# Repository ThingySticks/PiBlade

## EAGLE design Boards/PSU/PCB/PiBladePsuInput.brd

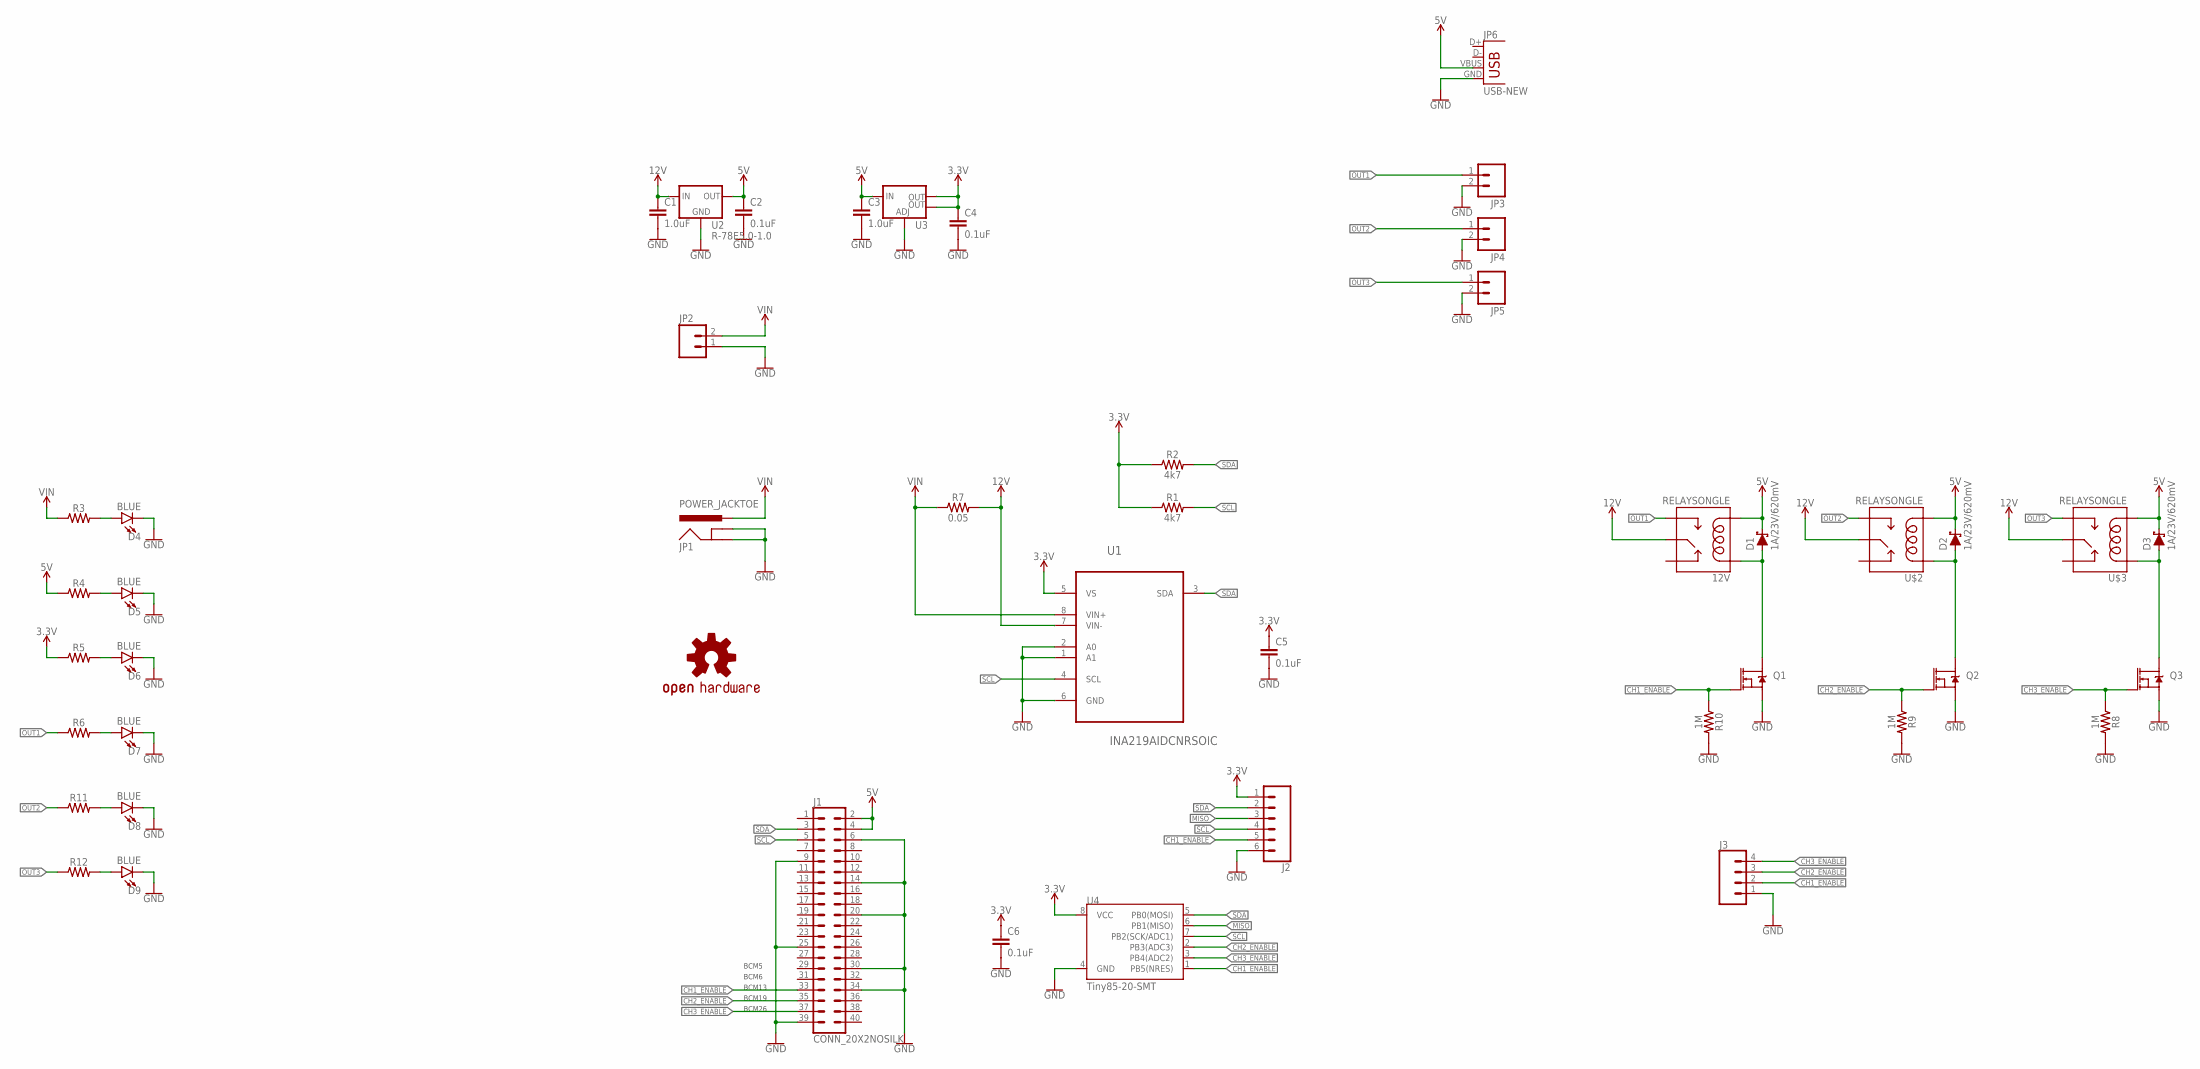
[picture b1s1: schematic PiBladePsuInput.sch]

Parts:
12V: RELAYSONGLE; SRD-5VDC-SL-C
C1, C3: 1.0uF; 0805
C2, C4, C5, C6: 0.1uF; 0805
D1, D2, D3: 1A/23V/620mV; SOD-323
D4, D5, D6, D7, D8, D9: BLUE; LED-1206
J1: CONN_20X2NOSILK; 2X20_NOSILK
J2: CONN_06SMD-1MM; 1X06-1MM
J3: CONN_04SMD2; 1X04_1MM_RA
JP1: POWER_JACKTOE; POWER_JACK_SMD_OVERPASTE_TOE
JP2, JP3, JP4, JP5: M025MM; SCREWTERMINAL-5MM-2
JP6: USB-NEW; USB-A-VERTICAL
LOGO1: OSHW-LOGOM; OSHW-LOGO-M
Q1, Q2, Q3: 220mA/50V/3.5Ω; SOT23-3
R1, R2: 4k7; 0805
R3, R4, R5, R6, R11, R12: 0805
R7: 0.05; 2512
R8, R9, R10: 1M; 0805
U1: INA219AIDCNRSOIC; SO08
U2: R-78E5.0-1.0; DC-DC_CONVERTER_78XX
U3: V_REG_LM1117SOT223; SOT223
U4: Tiny85-20-SMT; SO08-EIAJ
U$2, U$3: RELAYSONGLE; SRD-5VDC-SL-C

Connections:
3.3V: C4.1, C5.1, C6.1, J2.1, R1.1, R2.1, R5.1, U1.5 (VS), U3.2 (OUT), U3.4 (OUT), U4.8 (VCC)
5V: 12V.COIL2, C2.1, C3.1, D1.C, D2.C, D3.C, J1.2, J1.4, JP6.VBUS, R4.1, U2.VOUT (OUT), U3.3 (IN), U$2.COIL2, U$3.COIL2
12V: 12V.COMMON (MAIN), C1.1, R7.P$2 (2), U1.7 (VIN-), U2.VIN (IN), U$2.COMMON (MAIN), U$3.COMMON (MAIN)
CH1_ENABLE: J1.33, J2.5, J3.2, Q1.1 (G), R10.1, U4.1 (PB5(NRES))
CH2_ENABLE: J1.35, J3.3, Q2.1 (G), R9.1, U4.2 (PB3(ADC3))
CH3_ENABLE: J1.37, J3.4, Q3.1 (G), R8.1, U4.3 (PB4(ADC2))
GND: C1.2, C2.2, C3.2, C4.2, C5.2, C6.2, D4.C, D5.C, D6.C, D7.C, D8.C, D9.C, J1.6, J1.9, J1.14, J1.20, J1.25, J1.30, J1.34, J1.39, J2.6, J3.1, JP1.GND (GNDBREAK), JP1.P$4 (GND), JP2.1, JP3.2, JP4.2, JP5.2, JP6.GND, Q1.2 (S), Q2.2 (S), Q3.2 (S), R8.2, R9.2, R10.2, U1.1 (A1), U1.2 (A0), U1.6 (GND), U2.GND, U3.1 (ADJ), U4.4 (GND)
MISO: J2.3, U4.6 (PB1(MISO))
unnamed: D4.A, R3.2
unnamed: D6.A, R5.2
unnamed: D7.A, R6.2
unnamed: D5.A, R4.2
unnamed: D8.A, R11.2
unnamed: D9.A, R12.2
unnamed: D3.A, Q3.3 (D), U$3.COIL1
unnamed: D2.A, Q2.3 (D), U$2.COIL1
unnamed: 12V.COIL1, D1.A, Q1.3 (D)
OUT1: 12V.OPEN (NO), JP3.1, R6.1
OUT2: JP4.1, R11.1, U$2.OPEN (NO)
OUT3: JP5.1, R12.1, U$3.OPEN (NO)
SCL: J1.5, J2.4, R1.2, U1.4 (SCL), U4.7 (PB2(SCK/ADC1))
SDA: J1.3, J2.2, R2.2, U1.3 (SDA), U4.5 (PB0(MOSI))
VIN: JP1.VIN0 (PWR), JP2.2, R3.1, R7.P$1 (1), U1.8 (VIN+)

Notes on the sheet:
BCM13
BCM6
BCM5
BCM26
BCM19

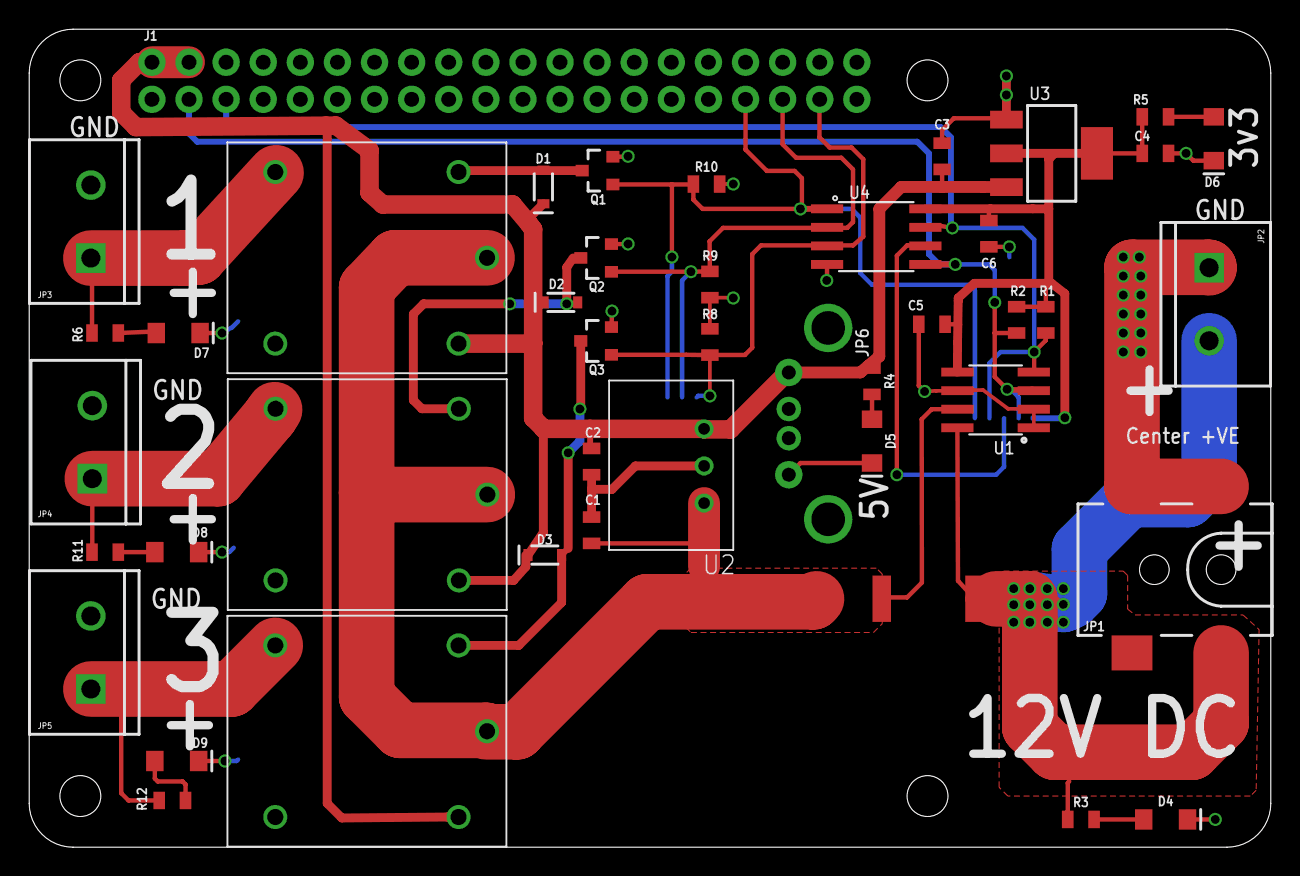
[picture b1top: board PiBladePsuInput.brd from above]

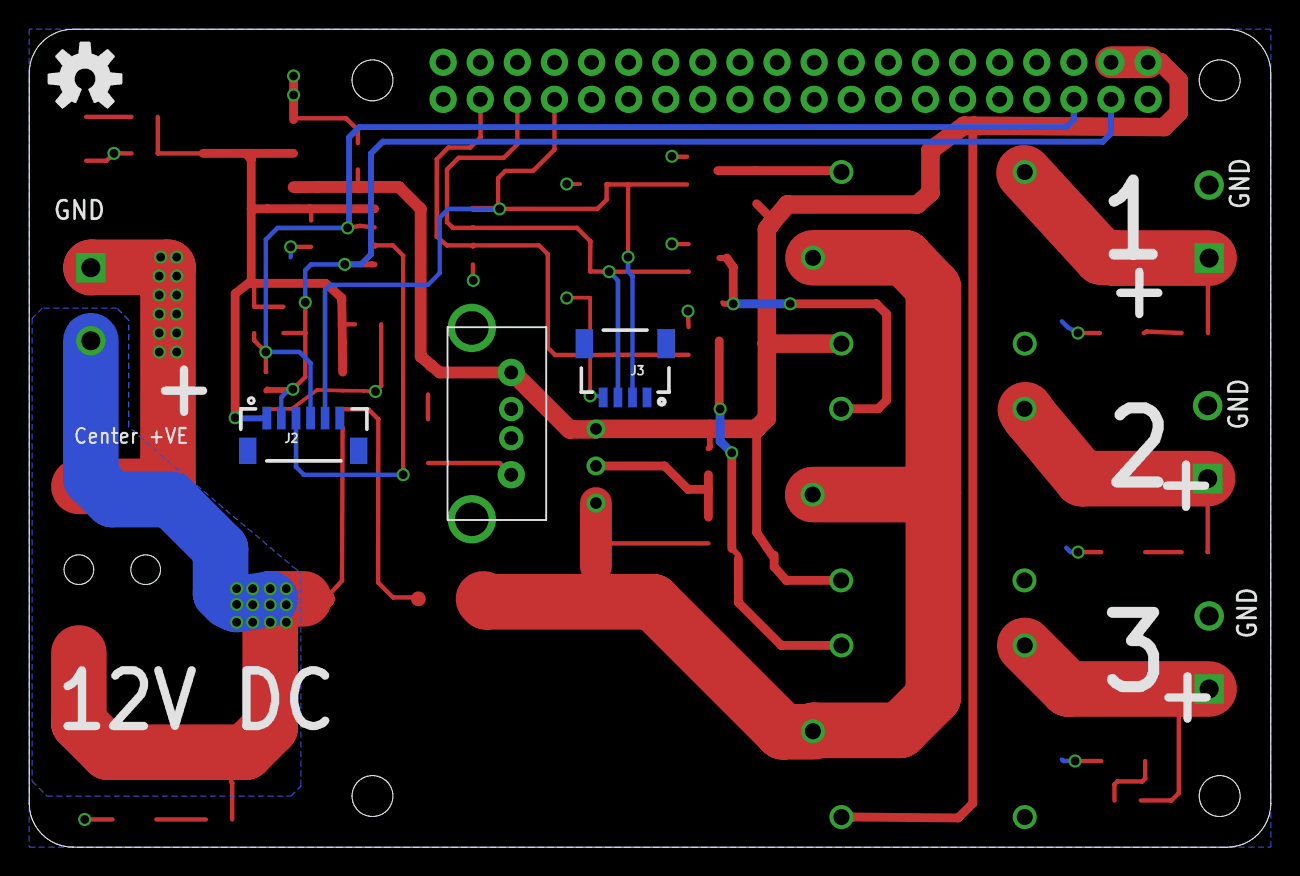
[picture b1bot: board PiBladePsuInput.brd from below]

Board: 2 copper layers, 85.0 x 56.0 mm, 47 parts (2 on the bottom side), 23 nets.

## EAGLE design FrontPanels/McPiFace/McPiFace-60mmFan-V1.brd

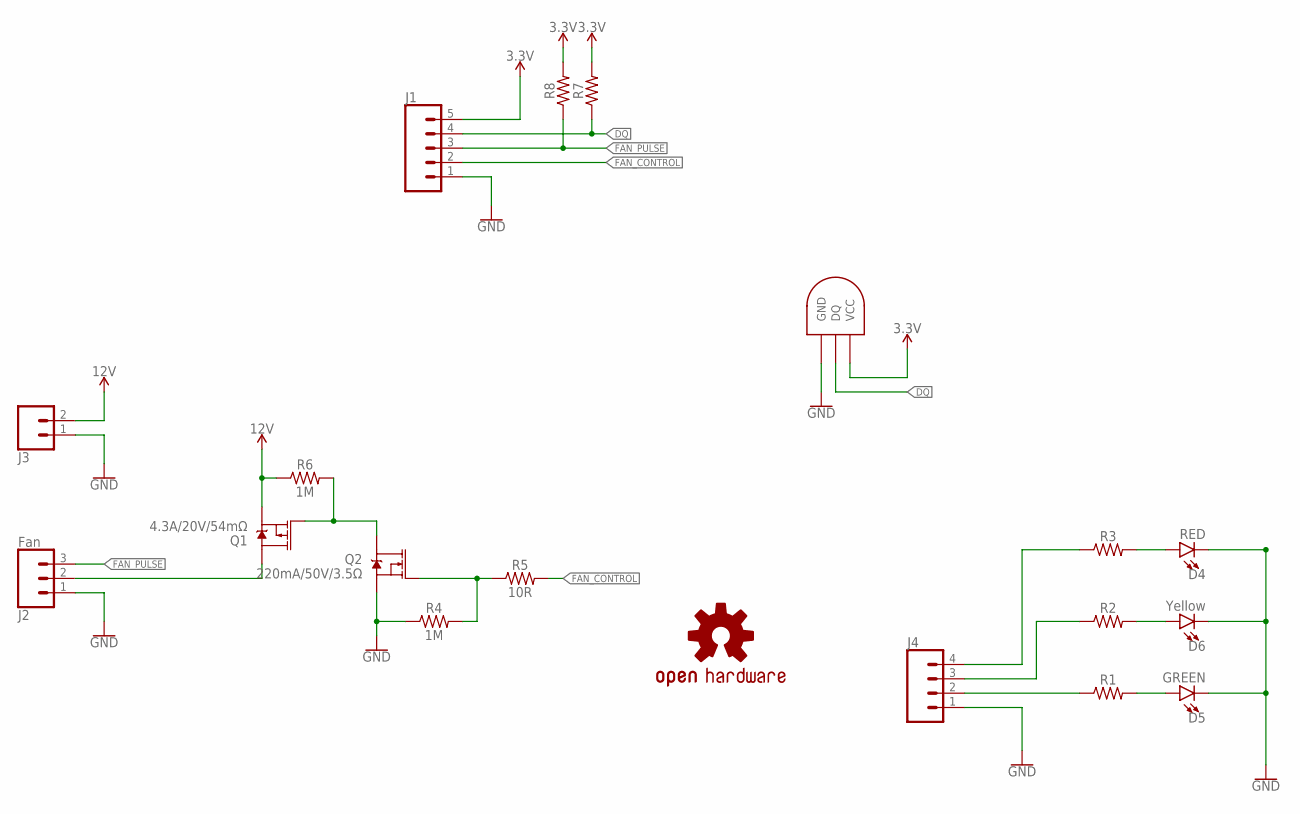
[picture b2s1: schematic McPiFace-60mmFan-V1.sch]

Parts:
D4: RED; LED-1206
D5: GREEN; LED-1206
D6: Yellow; LED-1206
J1: CONN_05SMD; 1X05_1MM
J2: Fan; JST-3-SMD
J3: CONN_02-JST-2MM-SMT; JST-2-SMD
J4: CONN_04SMD2; 1X04_1MM_RA
LOGO1: OSHW-LOGOL; OSHW-LOGO-L
Q1: 4.3A/20V/54mΩ; SOT23-3
Q2: 220mA/50V/3.5Ω; SOT23-3
R1, R2, R3: 1206
R4, R6: 1M; 0805
R5: 10R; 0805
R7, R8: 0805
U$1: DS1820SOIC; DS18B20_SOIC

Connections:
3.3V: J1.5, R7.2, R8.2, U$1.VCC
12V: J3.2 (1), Q1.2 (S), R6.1
DQ: J1.4, R7.1, U$1.DQ
FAN_CONTROL: J1.2, R5.2
FAN_PULSE: J1.3, J2.3 (1), R8.1
GND: D4.C, D5.C, D6.C, J1.1, J2.1 (3), J3.1 (2), J4.1, Q2.2 (S), R4.1, U$1.GND
unnamed: D4.A, R3.2
unnamed: D6.A, R2.2
unnamed: D5.A, R1.2
unnamed: J4.2, R1.1
unnamed: J4.3, R2.1
unnamed: J4.4, R3.1
unnamed: J2.2, Q1.3 (D)
unnamed: Q1.1 (G), Q2.3 (D), R6.2
unnamed: Q2.1 (G), R4.2, R5.1

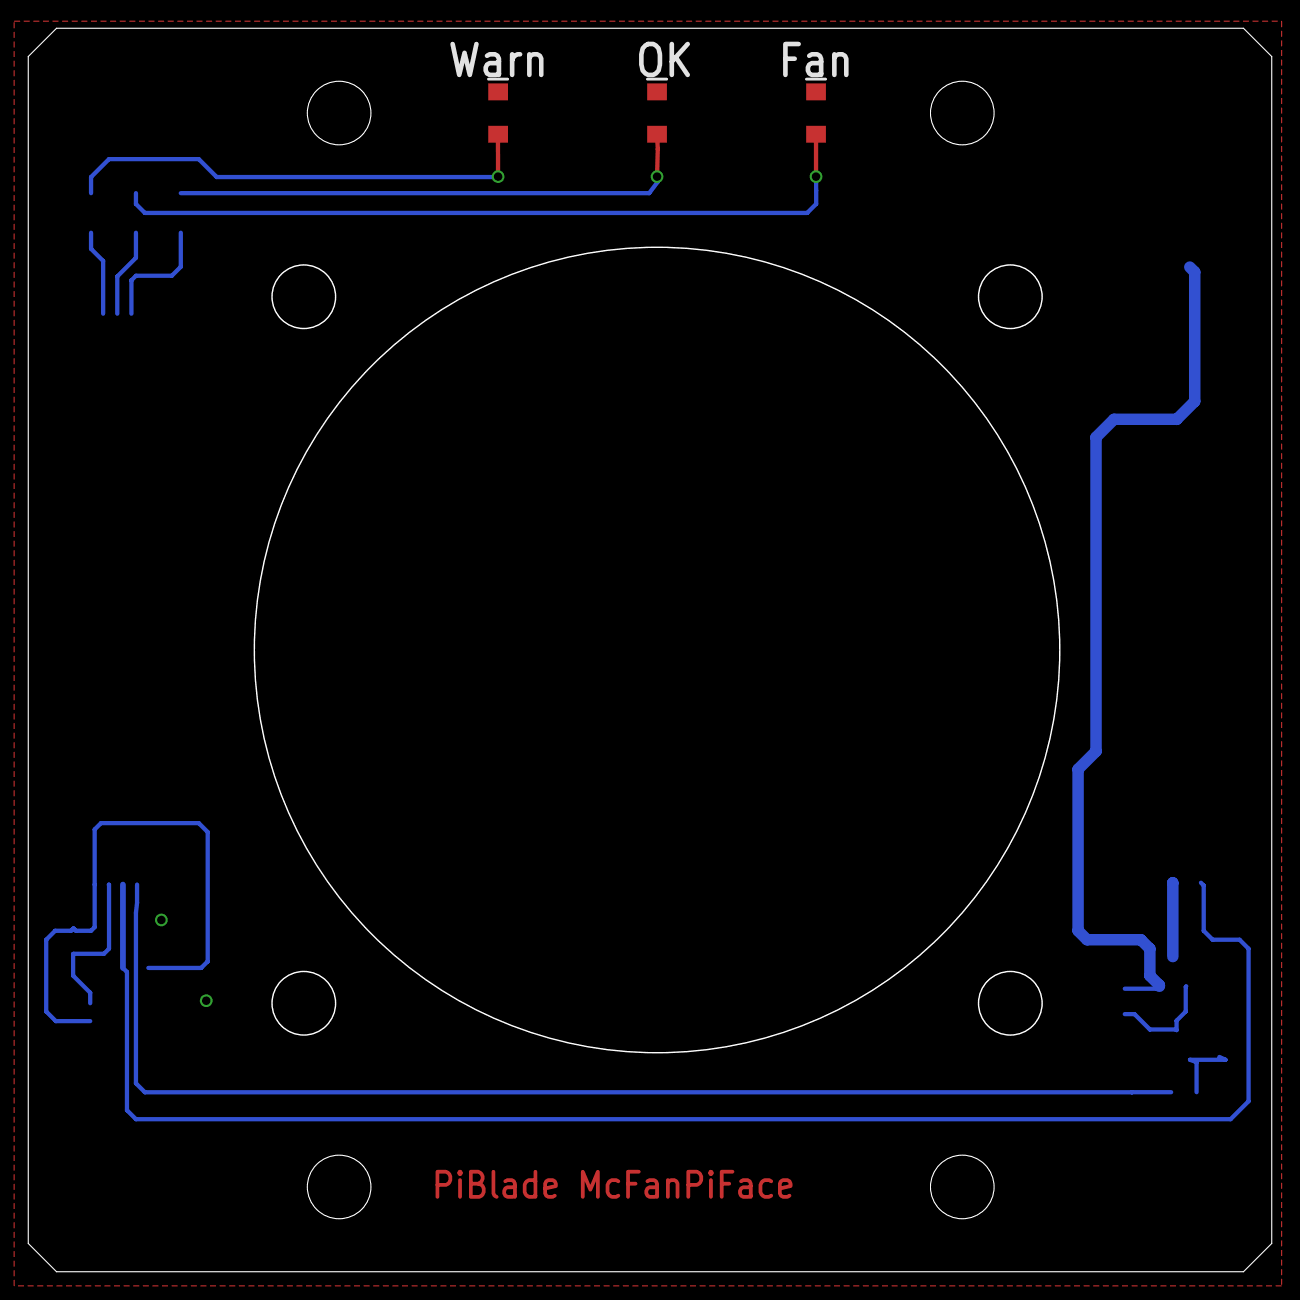
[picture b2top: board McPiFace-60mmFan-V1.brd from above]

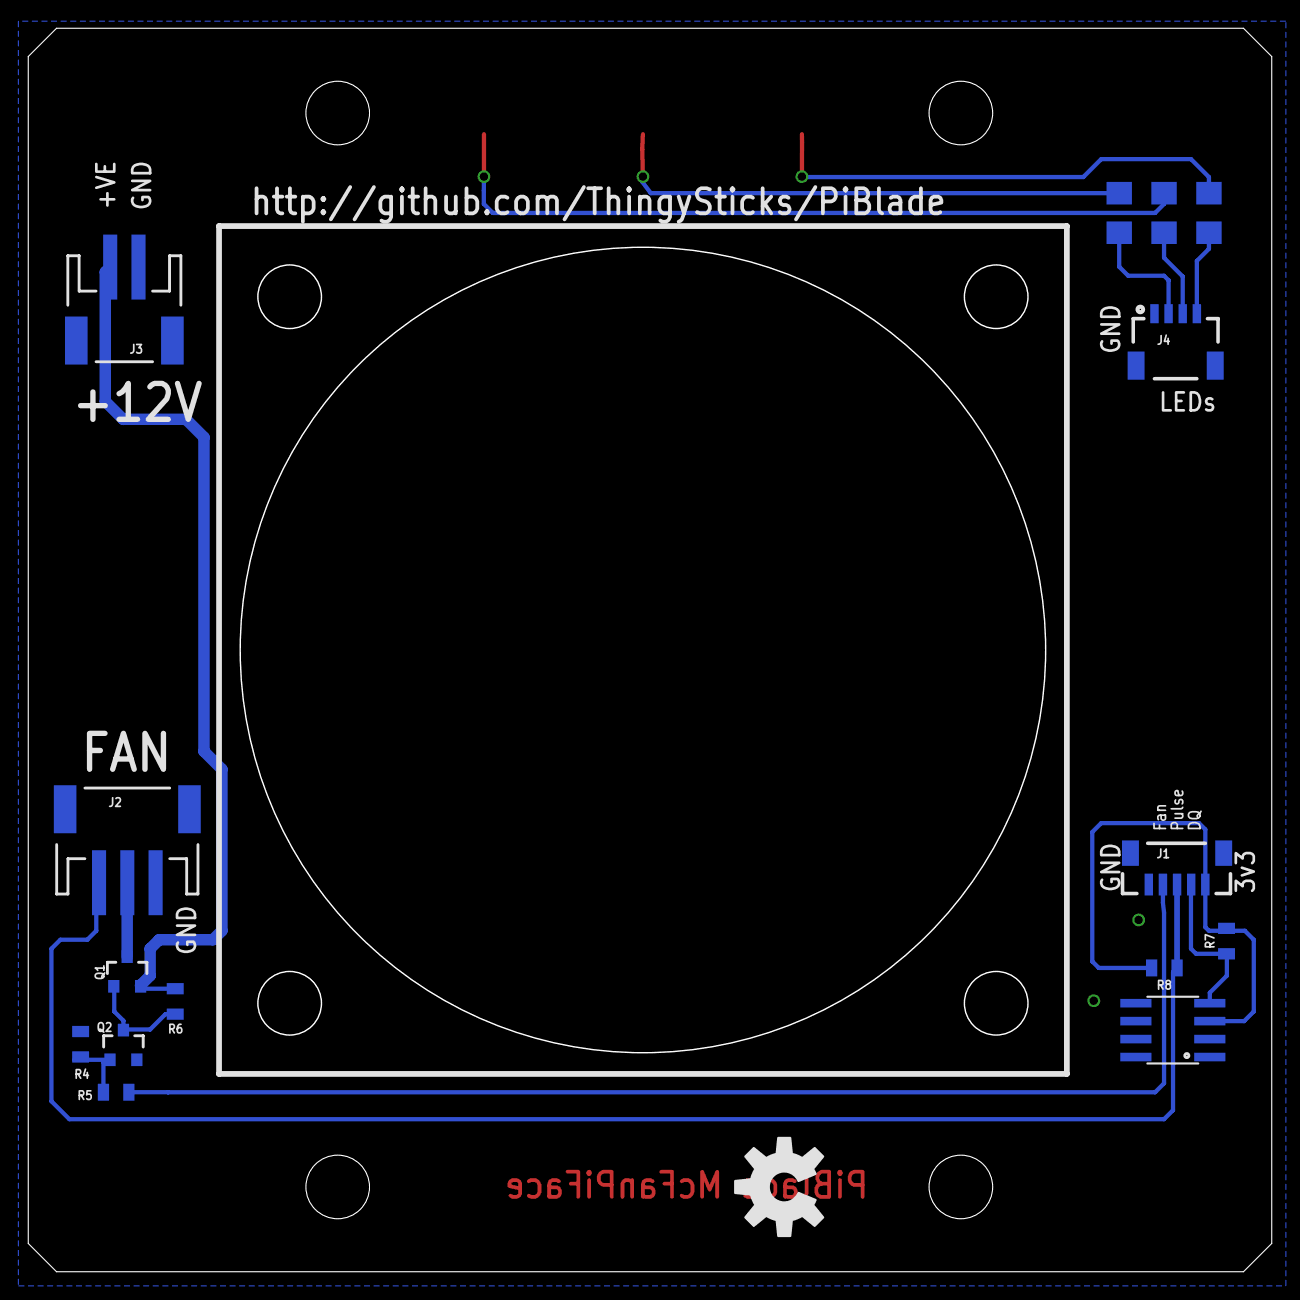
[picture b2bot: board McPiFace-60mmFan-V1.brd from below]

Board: 2 copper layers, 88.0 x 88.0 mm, 19 parts (16 on the bottom side), 15 nets.

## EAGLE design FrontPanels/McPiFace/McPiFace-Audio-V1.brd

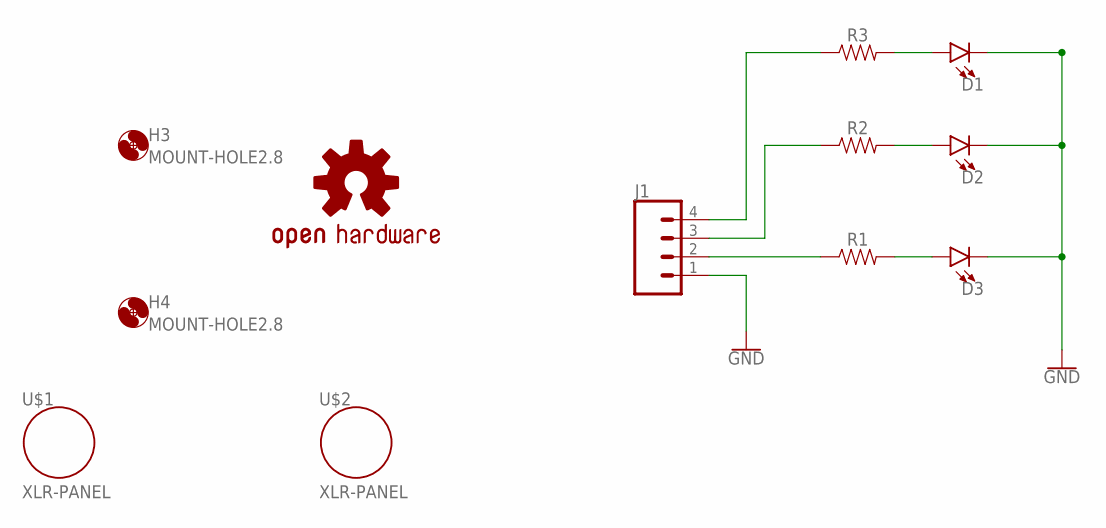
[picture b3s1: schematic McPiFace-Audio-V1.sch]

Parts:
D1, D2, D3: LED1206-BOTTOM-1.6MM; LED-1206-BOTTOM-1.6MM
H3, H4: MOUNT-HOLE2.8; 2,8
J1: CONN_04SMD2; 1X04_1MM_RA
LOGO1: OSHW-LOGOL; OSHW-LOGO-L
R1, R2, R3: 1206
U$1, U$2: XLR-PANEL; NC3FD-V-BAG-PANEL-COUTOUT

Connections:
GND: D1.C, D2.C, D3.C, J1.1
unnamed: D1.A, R3.2
unnamed: D2.A, R2.2
unnamed: D3.A, R1.2
unnamed: J1.2, R1.1
unnamed: J1.3, R2.1
unnamed: J1.4, R3.1

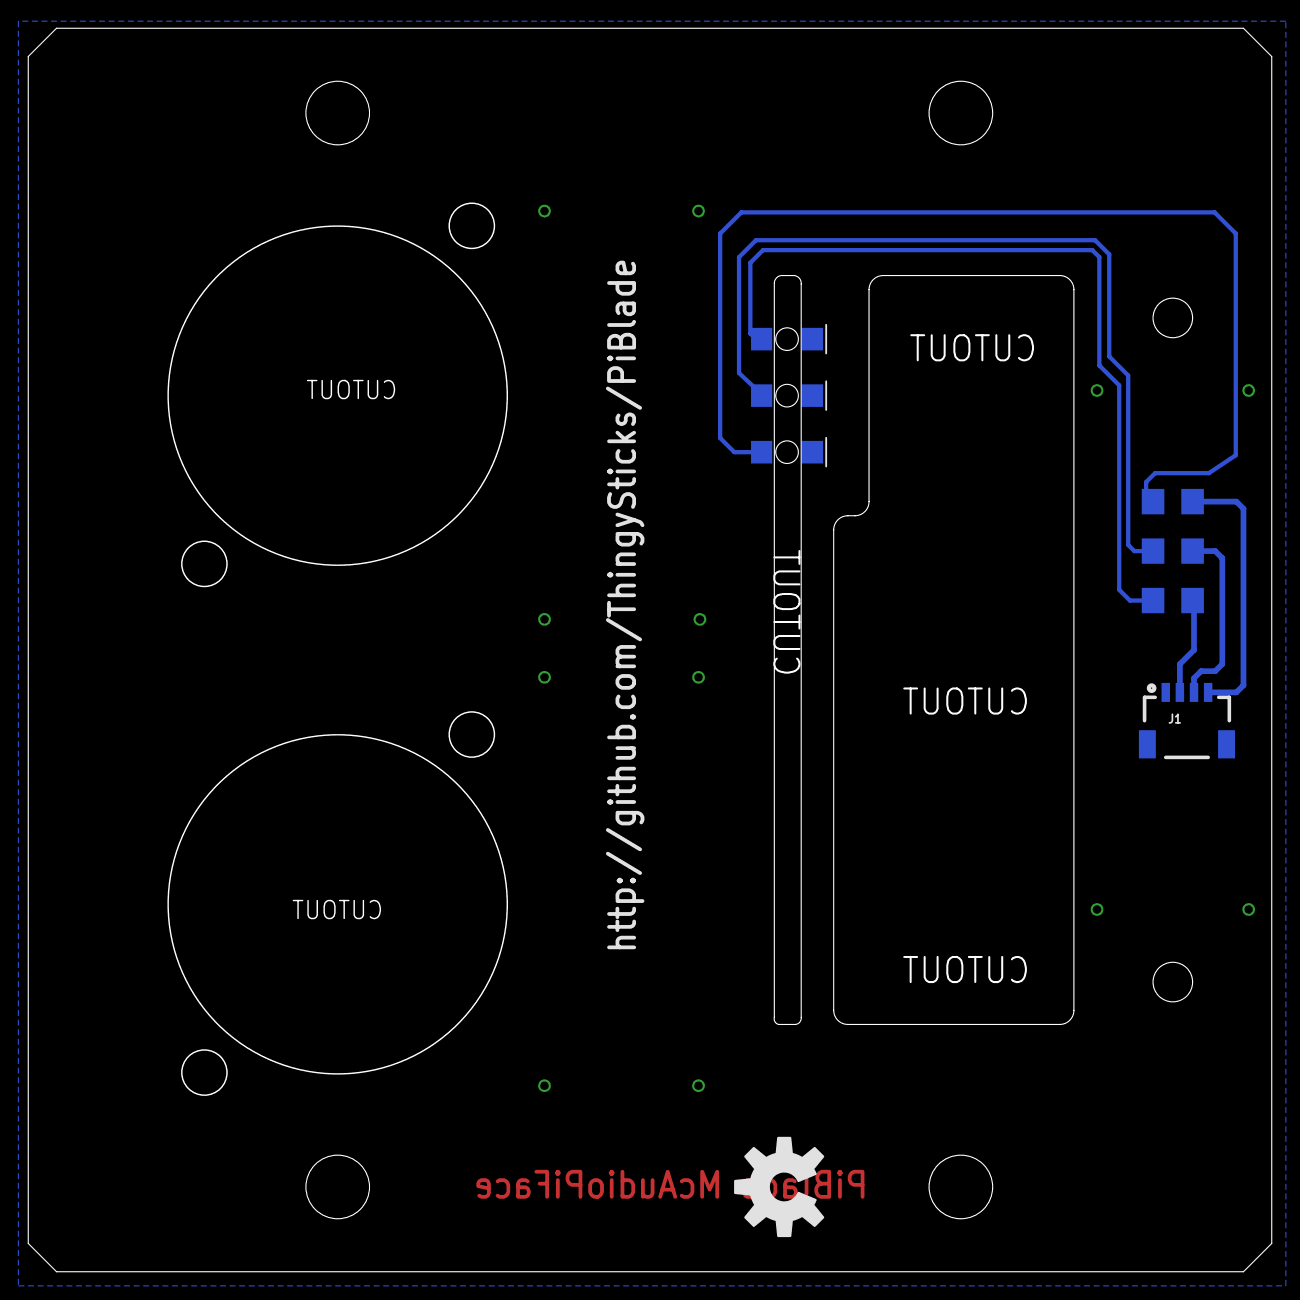
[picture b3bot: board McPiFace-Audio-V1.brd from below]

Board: 2 copper layers, 88.0 x 88.0 mm, 12 parts (8 on the bottom side), 7 nets.

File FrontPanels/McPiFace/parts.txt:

Partlist

Exported from McParticleEthernetFace-V1.brd at 25/01/2019 12:06

EAGLE Version 7.4.0 Copyright (c) 1988-2015 CadSoft

Assembly variant: 

Part     Value          Package               Library             Position (mm)         Orientation

D1                      LED-1206-BOTTOM-1.6MM ThingySticks        (32.54 67.58)         MR90
D2                      LED-1206-BOTTOM-1.6MM ThingySticks        (37.04 67.58)         MR90
D3                      LED-1206-BOTTOM-1.6MM ThingySticks        (41.54 67.58)         MR90
J1                      1X04_1MM_RA           SparkFun-Connectors (39.64 58.68)         MR0
R1                      0805                  SparkFun-Resistors  (41.54 62.18)         MR90
R2                      0805                  SparkFun-Resistors  (37.04 62.18)         MR90
R3                      0805                  SparkFun-Resistors  (32.54 62.18)         MR90

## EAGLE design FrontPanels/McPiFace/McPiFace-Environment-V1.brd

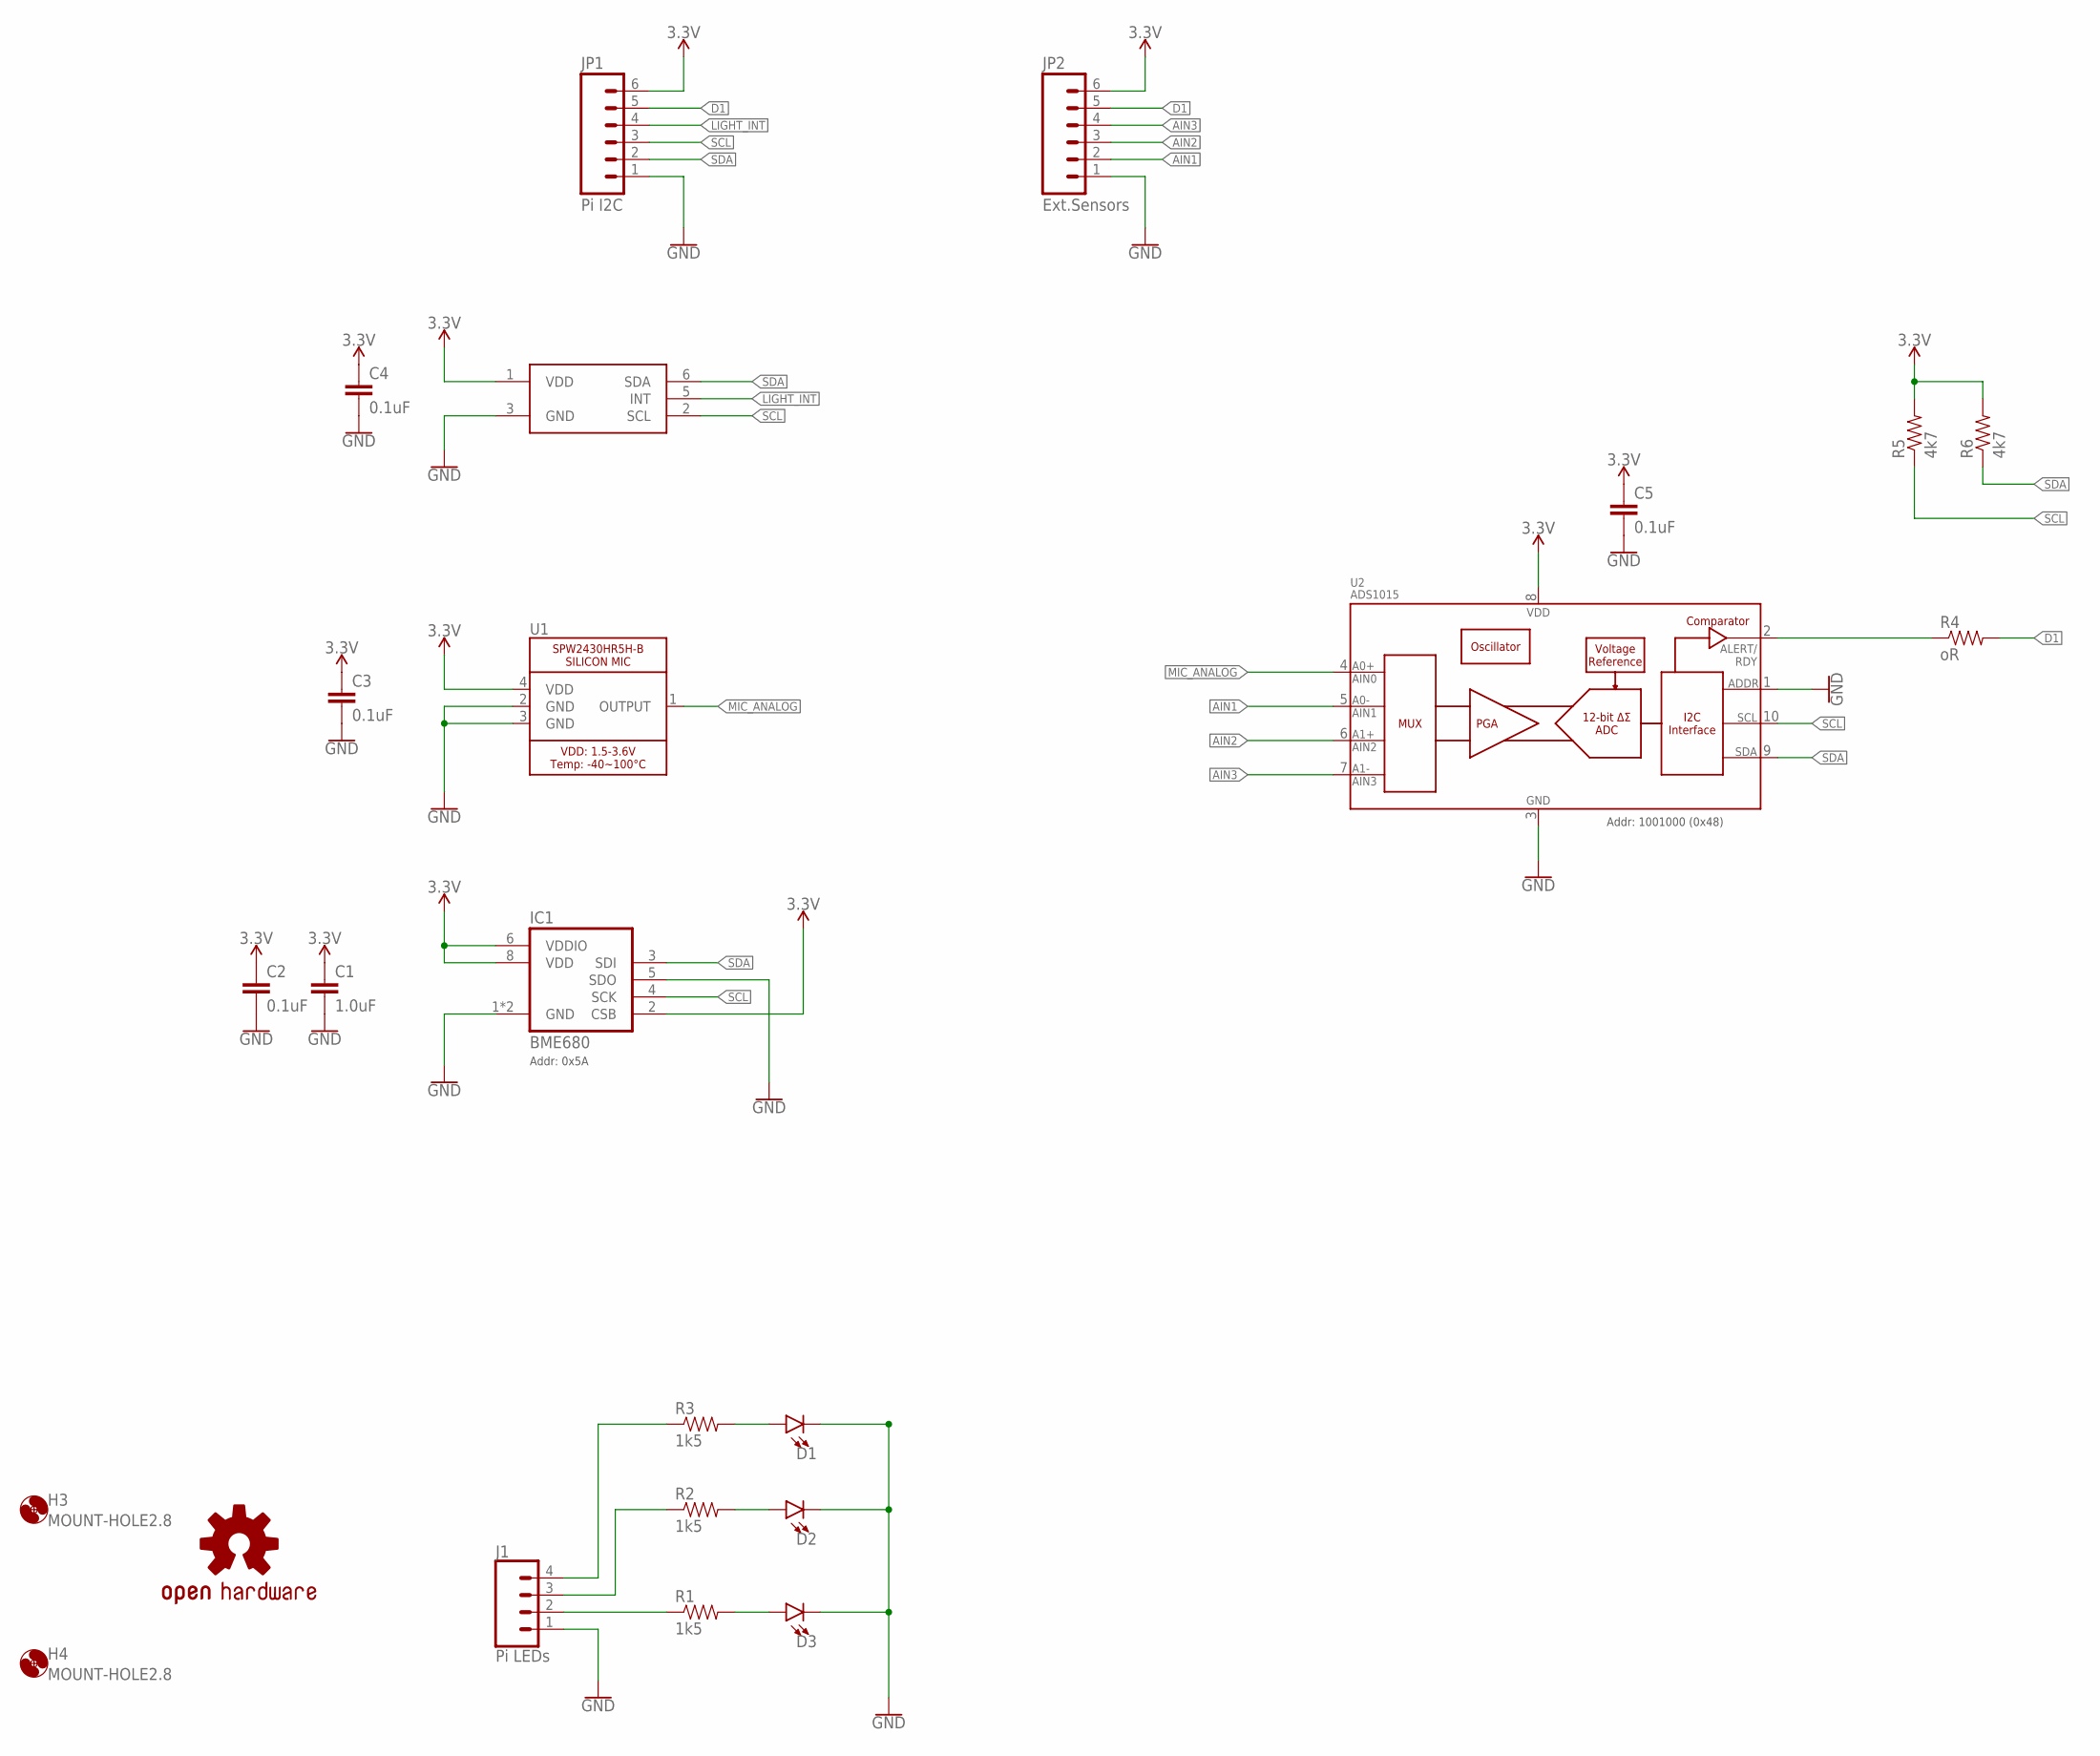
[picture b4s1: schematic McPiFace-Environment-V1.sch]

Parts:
C1: 1.0uF; 0805
C2, C3, C4, C5: 0.1uF; 0805
D1, D2, D3: LED1206-BOTTOM-1.6MM; LED-1206-BOTTOM-1.6MM
H3, H4: MOUNT-HOLE2.8; 2,8
IC1: BME680
J1: Pi LEDs; 1X04_1MM_RA
JP1: Pi I2C; 1X06-1MM
JP2: Ext.Sensors; 1X06-1MM
LOGO1: OSHW-LOGOL; OSHW-LOGO-L
R1, R2, R3: 1k5; 0805
R4: oR; 0805
R5, R6: 4k7; 0805
U1: SPW2430HR5H-B
U2: ADS1015; MSOP10
U$1: TCS3472; FN-6

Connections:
3.3V: C1.1, C2.1, C3.1, C4.1, C5.1, IC1.2 (CSB), IC1.6 (VDDIO), IC1.8 (VDD), JP1.6, JP2.6, R5.2, R6.2, U1.4 (VDD), U2.8 (VDD), U$1.1 (VDD)
AIN1: JP2.2, U2.5 (AIN1)
AIN2: JP2.3, U2.6 (AIN2)
AIN3: JP2.4, U2.7 (AIN3)
ALERT: R4.1, U2.2 (ALERT/RDY)
D1: JP1.5, JP2.5, R4.2
GND: C1.2, C2.2, C3.2, C4.2, C5.2, D1.C, D2.C, D3.C, IC1.1 (GND), IC1.5 (SDO), IC1.7 (GND), J1.1, JP1.1, JP2.1, U1.2 (GND), U1.3 (GND), U2.1 (ADDR), U2.3 (VSS), U$1.3 (GND)
LIGHT_INT: JP1.4, U$1.5 (INT)
MIC_ANALOG: U1.1 (OUTPUT), U2.4 (AIN0)
unnamed: D1.A, R3.2
unnamed: D2.A, R2.2
unnamed: D3.A, R1.2
unnamed: J1.2, R1.1
unnamed: J1.3, R2.1
unnamed: J1.4, R3.1
SCL: IC1.4 (SCK), JP1.3, R5.1, U2.10 (SCL), U$1.2 (SCL)
SDA: IC1.3 (SDI), JP1.2, R6.1, U2.9 (SDA), U$1.6 (SDA)

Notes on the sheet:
Addr: 1001000 (0x48)
Addr: 0x5A

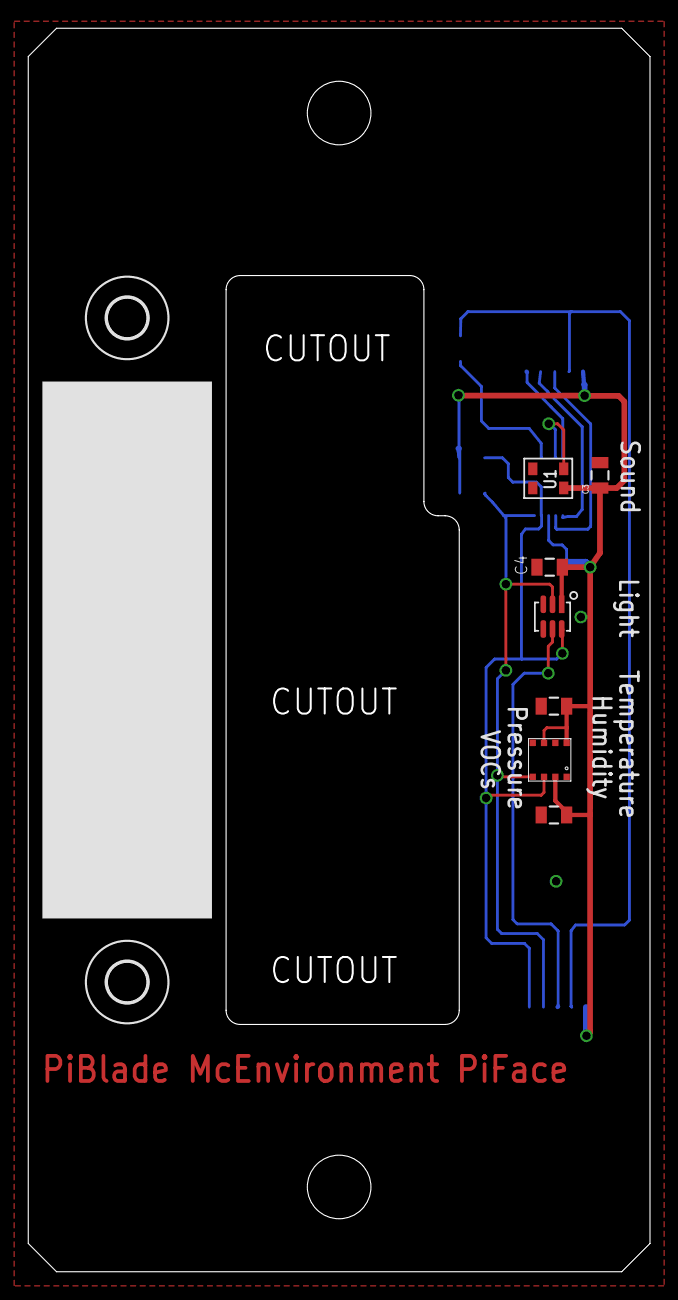
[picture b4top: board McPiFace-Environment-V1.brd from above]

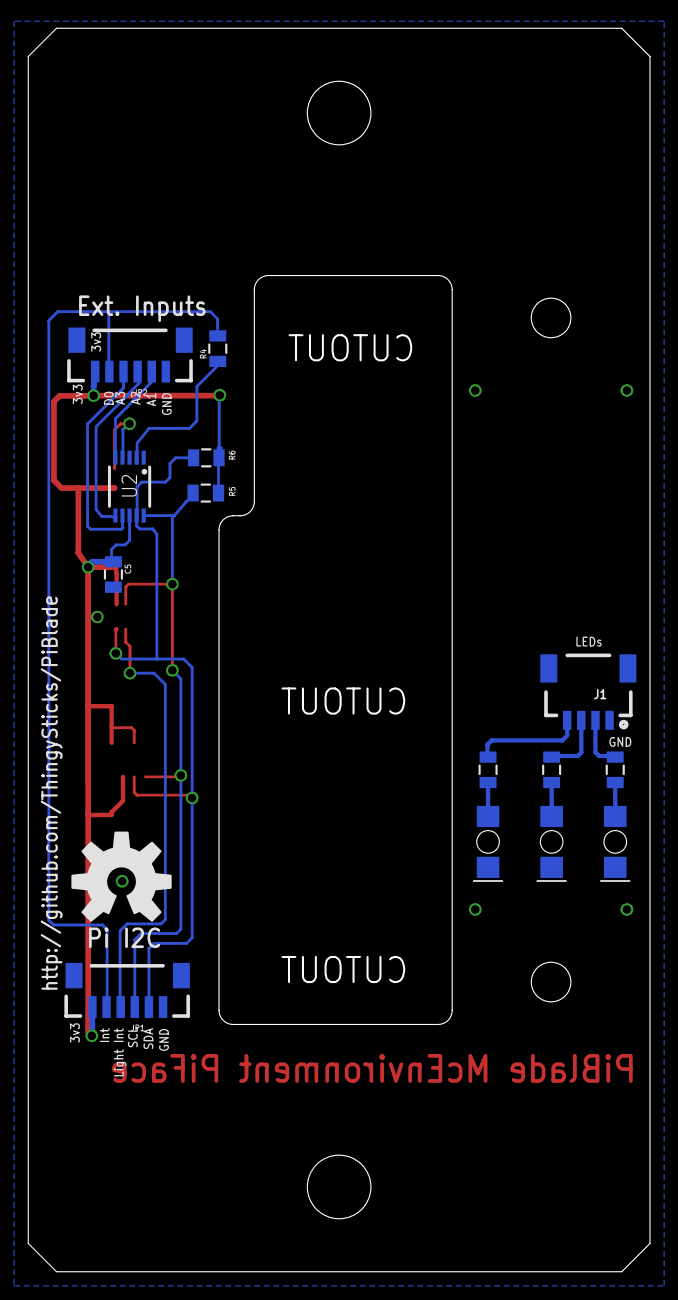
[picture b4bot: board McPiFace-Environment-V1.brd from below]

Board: 2 copper layers, 44.0 x 88.0 mm, 24 parts (15 on the bottom side), 17 nets.

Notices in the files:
parts and their libraries:
SparkFun-Connectors: Licensing: Creative Commons ShareAlike 4.0 International - https://creativecommons.org/licenses/by-sa/4.0
